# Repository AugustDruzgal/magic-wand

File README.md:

# magic-wand
Computers are magic!

This project contains the hardware and software used to create a magic wand that functions as a mouse for your computer!

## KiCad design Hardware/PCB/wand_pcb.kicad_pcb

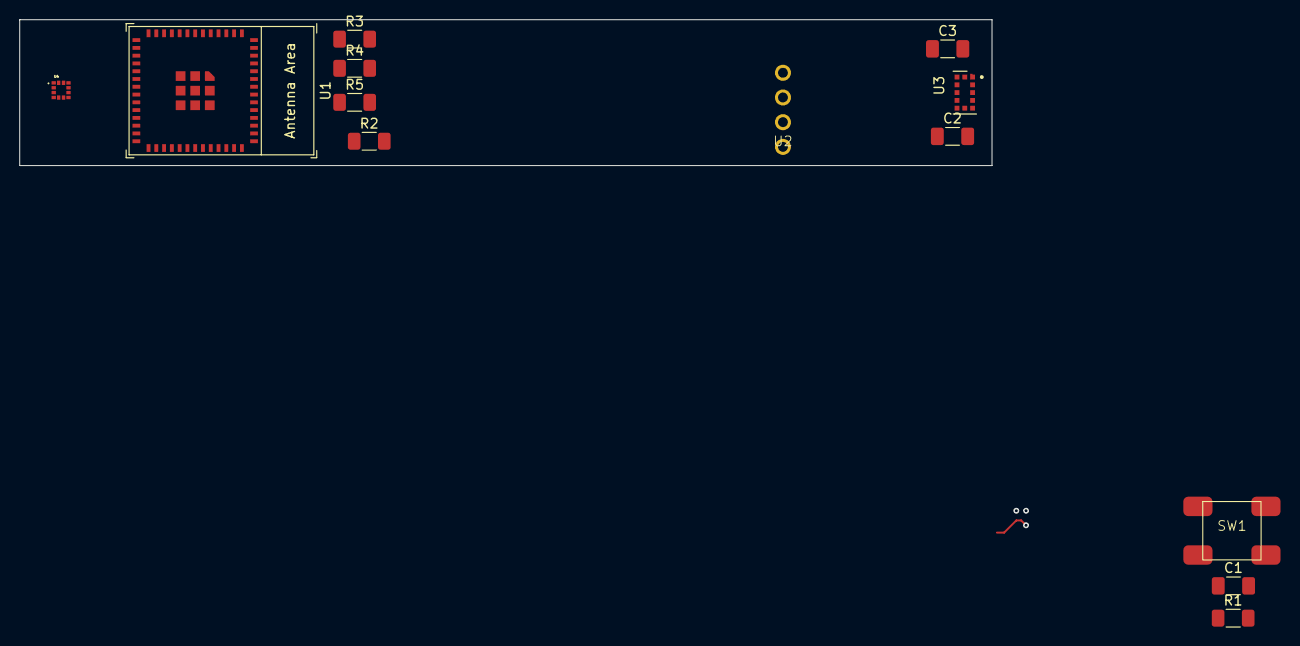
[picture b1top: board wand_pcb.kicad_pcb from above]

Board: 4 copper layers, 100.0 x 15.0 mm, 13 parts (0 on the bottom side), 10 nets.

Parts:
C1, C2, C3: C; C_1206_3216Metric_Pad1.33x1.80mm_HandSolder
R1, R2, R3, R4, R5: R_US; R_1206_3216Metric_Pad1.30x1.75mm_HandSolder
SW1: SW_Push; 6x6x4.3 SMD button
U1: ESP32-MINI-1
U2: 4-pin header
U3: XCDR_VL53L4CXV0DH_1
U4: LSM303AHTR; LGA12R50P_200X200X100

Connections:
/3V: C2.2, C3.1, R2.1, R3.1, R4.1, R5.1, U3.1 (AVDDVCSEL), U3.11 (AVDD)
/3V3: R1.2, U1.3 (3V3), U2.4
/EN: C1.1, R1.1, SW1.1, U1.8 (EN/CHIP_PU)
/GND: C1.2, C2.1, C3.2, SW1.2, U1.1 (GND), U1.2 (GND), U1.27 (GND), U1.38 (GND), U1.39 (GND), U1.40 (GND), U1.41 (GND), U1.42 (GND), U1.43 (GND), U1.44 (GND), U1.45 (GND), U1.46 (GND), U1.47 (GND), U1.48 (GND), U1.49 (GND), U1.50 (GND), U1.51 (GND), U1.52 (GND), U1.53 (GND), U1.54 (GND), U1.55 (GND), U2.3, U3.2 (AVSSVCSEL), U3.3 (GND), U3.4 (GND2), U3.6 (GND3), U3.12 (GND4)
/RXD: U1.35 (U0RXD/GPIO3), U2.1
/TXD: U1.36 (U0TXD/GPIO1), U2.2
/VL_GPIO1: R3.2, U3.7 (GPIO1)
/VL_SCL: R5.2, U3.10 (SCL)
/VL_SDA: R4.2, U3.9 (SDA)
/VL_XSHUT: R2.2, U3.5 (XSHUT)

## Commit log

2025-09-03 In progress: Adding TOF distance sensor, 9-axis IMU, and supporting components to schematic
2025-09-03 working on power supply conversion
2026-01-11 Added accel, gyro, mag
